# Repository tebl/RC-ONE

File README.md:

# KIM-1 Replica Computer
Along the years I've built quite a few computers, some bought as kits from various vendors and some I've even designed myself based on designs described in good old books or other technical resources - above all, there's always been one I really wanted above all of them: the KIM-1! 

Originally created by MOS in order to show off their new 6502-processor, it was a success that tapped into a market they probably never knew themselves was growing into a force to be reckoned with - the homecomputing market! Later bought up by little-known typewriter-manufacturer *Commodore*, the KIM-1 is an iconic piece of hardware and since I can't afford to buy one I'll build one instead.

The original unit cost 245$ assembled with everything you needed to get started, it had six segment displays for outputting information and a 24-key keypad onboard. CPU ran at an incredible 1 Mhz, it had a complete monitor in 2K of ROM, 1K of static RAM as well as an additional 128 bytes of RAM. You got 15 additional I/O lines to play with, all on a single PCB.

# RC-ONE
I however don't have that amount of money to play with, PCB prices skyrocket past 100x100 mm so I've separated functionality into separate boards so that each version would cost only around 5$ per piece instead. It means it's no longer a single board computer, but if it means more people can build it as a fun project then that's a plus in my book. The main setup does not include the additional 15 I/O lines due to space requirements, but you can add those back to the system by including the 65K Expansion (in addition to the backplane module) if you want to. If you just want to play around with the system and try your hand at machine language coding, you can get started with the CPU board, UI board and a keypad module.

As a classic microcomputer, I've gone ahead and created the obligatory memory map for your perusal - the highlights are shown below, but you'll find the complete set of information in the documentation section ([ODS](https://github.com/tebl/RC-ONE/raw/master/documentation/memory_map.ods)- or [PDF](https://github.com/tebl/RC-ONE/raw/master/documentation/memory_map.pdf)-format). Some of the functions have been shifted physically, but in the end the system should be functionally identical to an original system and able to run code without requireing changes.

The system is highly expandable, with the [65K Expansion board](https://github.com/tebl/RC-ONE/tree/master/RC1%2065K%20Expansion) in place you'll get better utilization of the components already on the CPU board as well as the ability to add additional modules to the system with an additional backplane also in place. See *System modules* below for a list of modules required for a complete system, optional modules available as well as modules for other systems that are compatible with the RC-ONE computer.

A lot of the work I've done couldn't have been completed without the work previously done by Ruud Baltissen, you can compare the schematics he did for the original KIM-1 computer and his more modern recreation of it by studying his [Build your own KIM-1](http://www.baltissen.org/newhtm/buildkim.htm) page.

## Project status
The RC-ONE computer is operational, it can be used to enter and run code via the keypad and can output to the displays as expected and for many this will be all that's needed to have fun with it as a replica of the KIM-1. Some sections are still being worked on, mainly those that deal with the TTY mode and tape functionality - see [TODO](https://github.com/tebl/RC-ONE/blob/master/TODO.md) for an overview of things I'd like to see done sometime in the future!

## System modules
As mentioned earlier there are a few different modules available for the system, some will be required to make the system function and others is considered optional and can be added if you want that extra piece of 70s-technology to play around with. There may be additional modules in the project files, but the ones I've added here are the ones that can be considered ready. As modules are being worked on over time, I've also added an order link to the modules so that you can get the last version I know worked. For more information about the specific module, including schematic and a list of parts you'd need to build it - click the name of the module!

Note that due to the similarities with the [RC6502  Apple 1 Replica](https://github.com/tebl/RC6502-Apple-1-Replica), quite a few of the modules developed for that system will also work with the RC-ONE - the ones I've tested and use with the system have also been linked below.

| Module    | RC-ONE | RC-ONE 65K | Order |
| --------- | ------ | ---------- | ----- |
| [RC-ONE CPU](https://github.com/tebl/RC-ONE/tree/master/RC1%20CPU) | required | required | [PCBWay](https://www.pcbway.com/project/shareproject/RC_ONE_KIM_1_Replica__CPU_module_.html) |
| [RC-ONE User Interface](https://github.com/tebl/RC-ONE/tree/master/RC1%20UI) | required | required | [PCBWay](https://www.pcbway.com/project/shareproject/RC_ONE_KIM_1_Replica__UI_revision_C_.html) |
| [RC-ONE Keypad SX](https://github.com/tebl/RC-ONE/tree/master/RC1%20Keypad) | required * | required * | [PCBWay](https://www.pcbway.com/project/shareproject/RC_ONE_Keypad_SX.html?inviteid=88707) |
| [RC-ONE Keypad MX](https://github.com/tebl/RC-ONE/tree/master/RC1%20Keypad%20MX) | required * | required * | [PCBWay](https://www.pcbway.com/project/shareproject/RC_ONE_Keypad_MX.html) |
| [RC-ONE 65K Expansion](https://github.com/tebl/RC-ONE/tree/master/RC1%2065K%20Expansion) |  | required | [PCBWay](https://www.pcbway.com/project/shareproject/RC_ONE_65K_Expansion.html) |
| [RC-ONE 8K ExRAM](https://github.com/tebl/RC-ONE/tree/master/RC1%208K%20ExRAM) |  | optional | |
| [RC6502 Backplane](https://github.com/tebl/RC6502-Apple-1-Replica/tree/master/RC6502%20Backplane)  |  | required | [PCBWay](https://www.pcbway.com/project/shareproject/RC6502_Apple_1_Replica__Backplane_module_revision_A_.html?inviteid=88707) |
| [RC6502 Prototyping module](https://github.com/tebl/RC6502-Apple-1-Replica/tree/master/RC6502%20Prototyping) |  | optional | [PCBWay](https://www.pcbway.com/project/shareproject/RC6502_Apple_1_Replica__Module_prototyping_board_.html?inviteid=88707) |
| [6502 Project Platform](https://github.com/tebl/RC-Project-Board) | optional | optional | [PCBWay](https://www.pcbway.com/project/shareproject/6502_Project_Platform__RC6502__RC_ONE__RC6802_.html?inviteid=88707) |
| [6502 Games Board](https://github.com/tebl/RC-Project-Board/tree/master/projects/GB-001%20Game%20Board) | | optional** | [PCBWay](https://www.pcbway.com/project/shareproject/6502_Games_Board.html)
| [6502 Games Platform](https://github.com/tebl/RC-Project-Board/tree/master/platforms/PP%206502%20Game%20Board) | | optional** | [PCBWay](https://www.pcbway.com/project/shareproject/6502_Games_Platform.html)

*) Only one Keypad module is required, the MX version is a lot more comfortable to use though it comes at an increased cost.
**) You need [6502 Games Platform](https://github.com/tebl/RC-Project-Board/tree/master/platforms/PP%206502%20Game%20Board) and 6502 Game Board to build the 6502 Games hardware, originally created by Rodnay Zaks in his book [6502 Games](https://archive.org/details/6502GamesRodnayZaks/mode/2up). To use them with the RC-ONE you also require the [65K Expansion](https://github.com/tebl/RC-ONE/tree/master/RC1%2065K%20Expansion) installed.

If you would like to have a copy of one or more modules (usually 5$ per module), consider using the order links listed above - that way you also support the development of these boards while doing so. Alternatively, you can also zip up the contents of the export directory for each module and give that to your favourite PCB fabrication plant (I use [PCBWay](https://www.pcbway.com/setinvite.aspx?inviteid=88707) instead. Note that since I'm always tinkering with things, this repository may contain changes that I've not yet tested!

## Tell me more!
You'll find a lot of additional technical information belonging to each of the various modules by clicking on them from the table in the previous section, but those are mainly for reference when using or building them. For that reason I've also taken the time to write a somewhat acceptable attempt at a [manual](https://github.com/tebl/RC-ONE/blob/master/Manual.md), it should be able to get you started at both understanding not only how to use the computer, but also give you a more concise idea about what a KIM-1 computer (or replica) actually is.

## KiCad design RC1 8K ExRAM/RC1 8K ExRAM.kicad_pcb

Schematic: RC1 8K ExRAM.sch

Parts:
A1: Arduino_Nano_v3.x; Arduino_Nano
C1, C2, C3, C4, C5, C6, C7, C8: 100nF; C_Disc_D4.7mm_W2.5mm_P5.00mm
D1: BUSY; LED_D5.0mm
D2: DATA; LED_D5.0mm
D3: CLK; LED_D5.0mm
D4: 1n914; D_DO-35_SOD27_P7.62mm_Horizontal
J1: Expansion; Pin_Header_Angled_1x39_Pitch2.54mm
J2: ADDRESS; Pin_Header_Straight_2x09_Pitch2.54mm
JP1: USB_PWR; Pin_Header_Straight_1x02_Pitch2.54mm
JP2: ReadOnly; Pin_Header_Straight_1x03_Pitch2.54mm
R1, R2, R3: 220; R_Axial_DIN0207_L6.3mm_D2.5mm_P10.16mm_Horizontal
R4, R5, R6, R7: 10k; R_Axial_DIN0207_L6.3mm_D2.5mm_P10.16mm_Horizontal
U1: 74LS138; DIP-16_W7.62mm_Socket
U2: 74LS00; DIP-14_W7.62mm_Socket
U3, U4: 74HC595; DIP-16_W7.62mm_Socket
U5: HM62256BLP-7; DIP-28_W15.24mm_Socket
U6, U7: 74LS244; DIP-20_W7.62mm_Socket
U8: 74LS245; DIP-20_W7.62mm_Socket

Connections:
/8K1: J2.1, U1.14 (O1)
/8K2: J2.3, U1.13 (O2)
/8K3: J2.5, U1.12 (O3)
/8K4: J2.7, U1.11 (O4)
/8K5: J2.9, U1.10 (O5)
/8K6: J2.11, U1.9 (O6)
/8K7: J2.13, U1.7 (O7)
/A0: J1.16 (A0), U6.2 (I0a)
/A1: J1.15 (A1), U6.4 (I1a)
/A2: J1.14 (A2), U6.6 (I2a)
/A3: J1.13 (A3), U6.8 (I3a)
/A4: J1.12 (A4), U6.11 (I0b)
/A5: J1.11 (A5), U6.13 (I1b)
/A6: J1.10 (A6), U6.15 (I2b)
/A7: J1.9 (A7), U6.17 (I3b)
/A8: J1.8 (A8), U7.2 (I0a)
/A9: J1.7 (A9), U7.4 (I1a)
/A10: J1.6 (A10), U7.6 (I2a)
/A11: J1.5 (A11), U7.8 (I3a)
/A12: J1.4 (A12), U7.11 (I0b)
/A13: J1.3 (A13), U1.1 (A0)
/A14: J1.2 (A14), U1.2 (A1)
/A15: J1.1 (A15), U1.3 (A2)
/D0: J1.27 (D0), U8.18 (B0)
/D1: J1.28 (D1), U8.17 (B1)
/D2: J1.29 (D2), U8.16 (B2)
/D3: J1.30 (D3), U8.15 (B3)
/D4: J1.31 (D4), U8.14 (B4)
/D5: J1.32 (D5), U8.13 (B5)
/D6: J1.33 (D6), U8.12 (B6)
/D7: J1.34 (D7), U8.11 (B7)
/EX_A0: U3.15 (QA), U5.10, U6.18 (O0a)
/EX_A1: U3.1 (QB), U5.9, U6.16 (O1a)
/EX_A2: U3.2 (QC), U5.8, U6.14 (O2a)
/EX_A3: U3.3 (QD), U5.7, U6.12 (O3a)
/EX_A4: U3.4 (QE), U5.6, U6.9 (O0b)
/EX_A5: U3.5 (QF), U5.5, U6.7 (O1b)
/EX_A6: U3.6 (QG), U5.4, U6.5 (O2b)
/EX_A7: U3.7 (QH), U5.3, U6.3 (O3b)
/EX_A8: U4.15 (QA), U5.25, U7.18 (O0a)
/EX_A9: U4.1 (QB), U5.24, U7.16 (O1a)
/EX_A10: U4.2 (QC), U5.21, U7.14 (O2a)
/EX_A11: U4.3 (QD), U5.23, U7.12 (O3a)
/EX_A12: U4.4 (QE), U5.2, U7.9 (O0b)
/EX_A13: A1.19, R6.1, U5.26
/EX_A14: A1.20, R5.1, U5.1
/EX_D0: A1.9, U5.11, U8.2 (A0)
/EX_D1: A1.10, U5.12, U8.3 (A1)
/EX_D2: A1.11, U5.13, U8.4 (A2)
/EX_D3: A1.12, U5.15, U8.5 (A3)
/EX_D4: A1.13, U5.16, U8.6 (A4)
/EX_D5: A1.14, U5.17, U8.7 (A5)
/EX_D6: A1.15, U5.18, U8.8 (A6)
/EX_D7: A1.16, U5.19, U8.9 (A7)
/EX_R/~W: A1.21, JP2.2, R7.1, U5.27
/EX_~CS: A1.24, U5.20, U7.3 (O3b); also elsewhere on the board
/PHI2: J1.19 (PHI2), U1.6 (E3)
/R/~W: J1.24 (RW), U7.13 (I1b), U8.1 (A->B)
/RESET: A1.22, J1.20 (RESET)
BUSY: R1.2, U2.6
CONTROL: A1.8, R4.1, U2.4, U2.5, U2.9, U3.13 (G), U4.13 (G)
K0_EXT: J1.36 (RX), J2.15
K7_EXT: J1.37 (NMI), J2.17
unnamed: A1.27, D4.1, JP1.1
unnamed: D1.2, R1.1
unnamed: D2.2, R2.1
unnamed: D3.2, R3.1
unnamed: J2.2, J2.4, J2.6, J2.8, J2.10, J2.12, J2.14, J2.16, J2.18, U2.1, U2.2
unnamed: JP2.1, U7.5 (O2b)
unnamed: JP2.3, U7.7 (O1b)
unnamed: U2.3, U2.10
unnamed: U3.9 (~QH), U4.14 (SER)
SHIFT_CLK: A1.6, R3.2, U3.11 (SRCLK), U4.11 (SRCLK)
SHIFT_DATA: A1.5, R2.2, U3.14 (SER)
SHIFT_LATCH: A1.7, U3.12 (RCLK), U4.12 (RCLK)
VMEM: C5.1, R7.2, U5.28; also elsewhere on the board
~RC1_CS: U2.8, U6.1 (OEa), U6.19 (OEb), U7.1 (OEa), U7.17 (I3b), U7.19 (OEb), U8.19 (CE)

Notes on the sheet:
RC-ONE 8K ExRAM
$E000
$2000
$4000
$6000
$8000
$A000
$C000
RAM SELECT
ROM SELECT
HI allows 6502 access to RAM
RC-ONE is accessing data from memory.
Based on an idea for an EEPROM programmer by Ben Eater, this adapts the idea to loading data into static RAM via an Arduino Nano. The Nano can block the 6502 from accessing the memory while data is being loaded, ReadOnly jumper can be used to keep 6502 from being able to change the data.
ExRAM is controlling memory

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
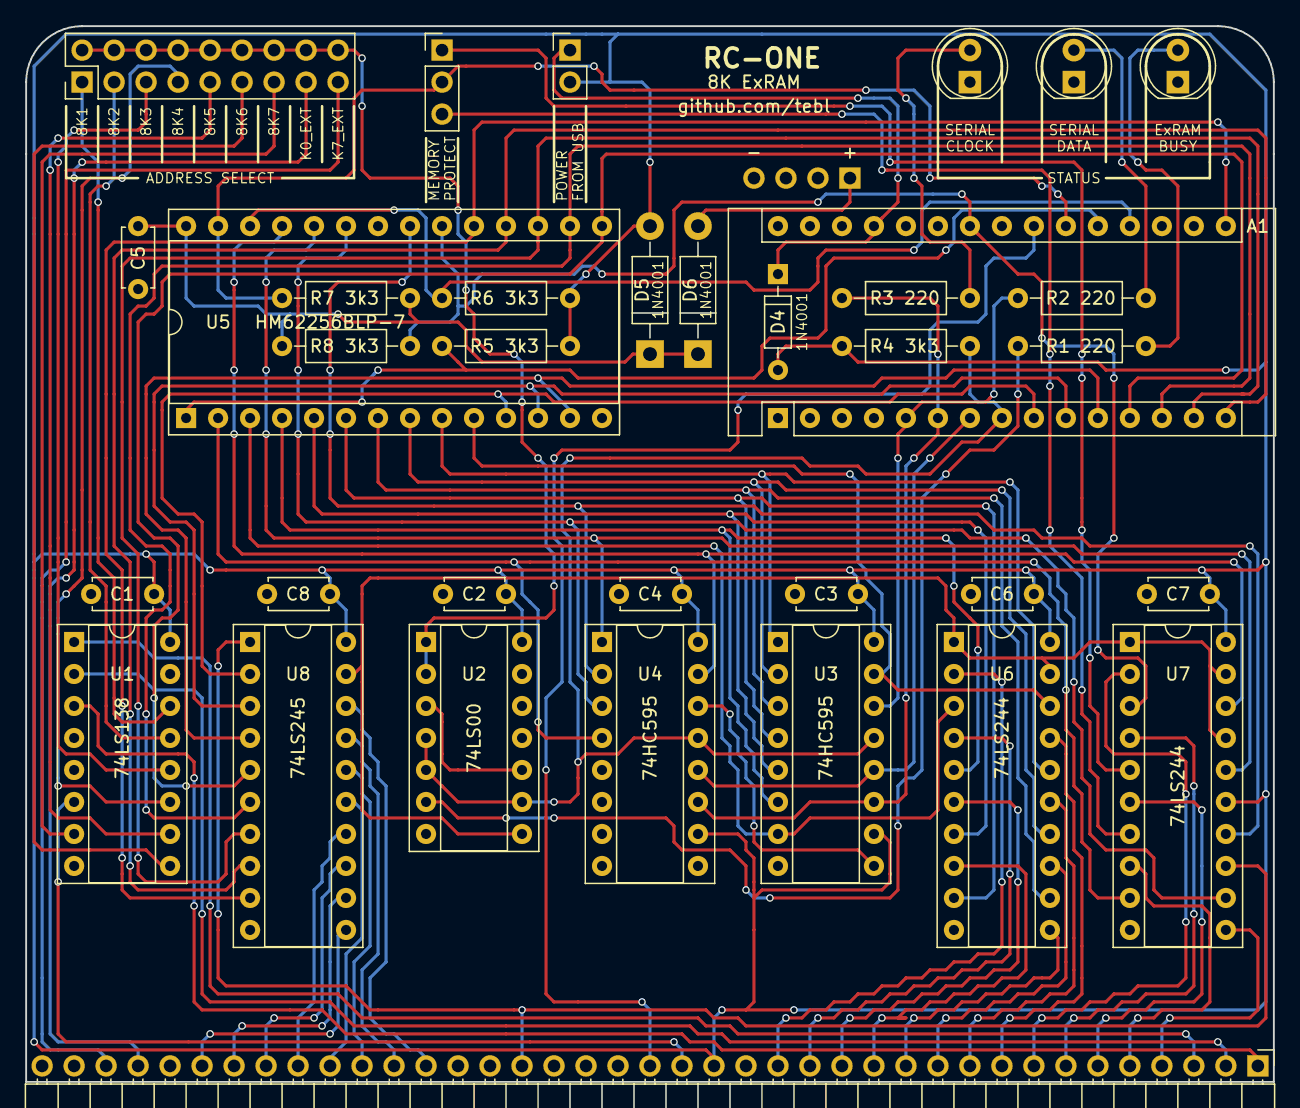
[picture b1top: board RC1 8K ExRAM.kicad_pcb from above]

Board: 2 copper layers, 99.1 x 83.8 mm, 36 parts (1 on the bottom side), 80 nets.

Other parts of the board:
D5, D6: 1N4001; D_DO-41_SOD81_P10.16mm_Horizontal
J3: BATTERY; Pin_Header_Angled_1x04_Pitch2.54mm
R8: 3k3; R_Axial_DIN0207_L6.3mm_D2.5mm_P10.16mm_Horizontal

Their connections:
/BATTERY: D6.2, J3.1
/EX_~CS: R8.1; also elsewhere on the board
VMEM: D5.1, D6.1, R8.2; also elsewhere on the board

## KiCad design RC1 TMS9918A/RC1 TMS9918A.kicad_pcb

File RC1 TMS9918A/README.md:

# RC-ONE TMS9918A

**This design is untested!**

Display card based on the TMS9918A chip created by Texas Instruments.

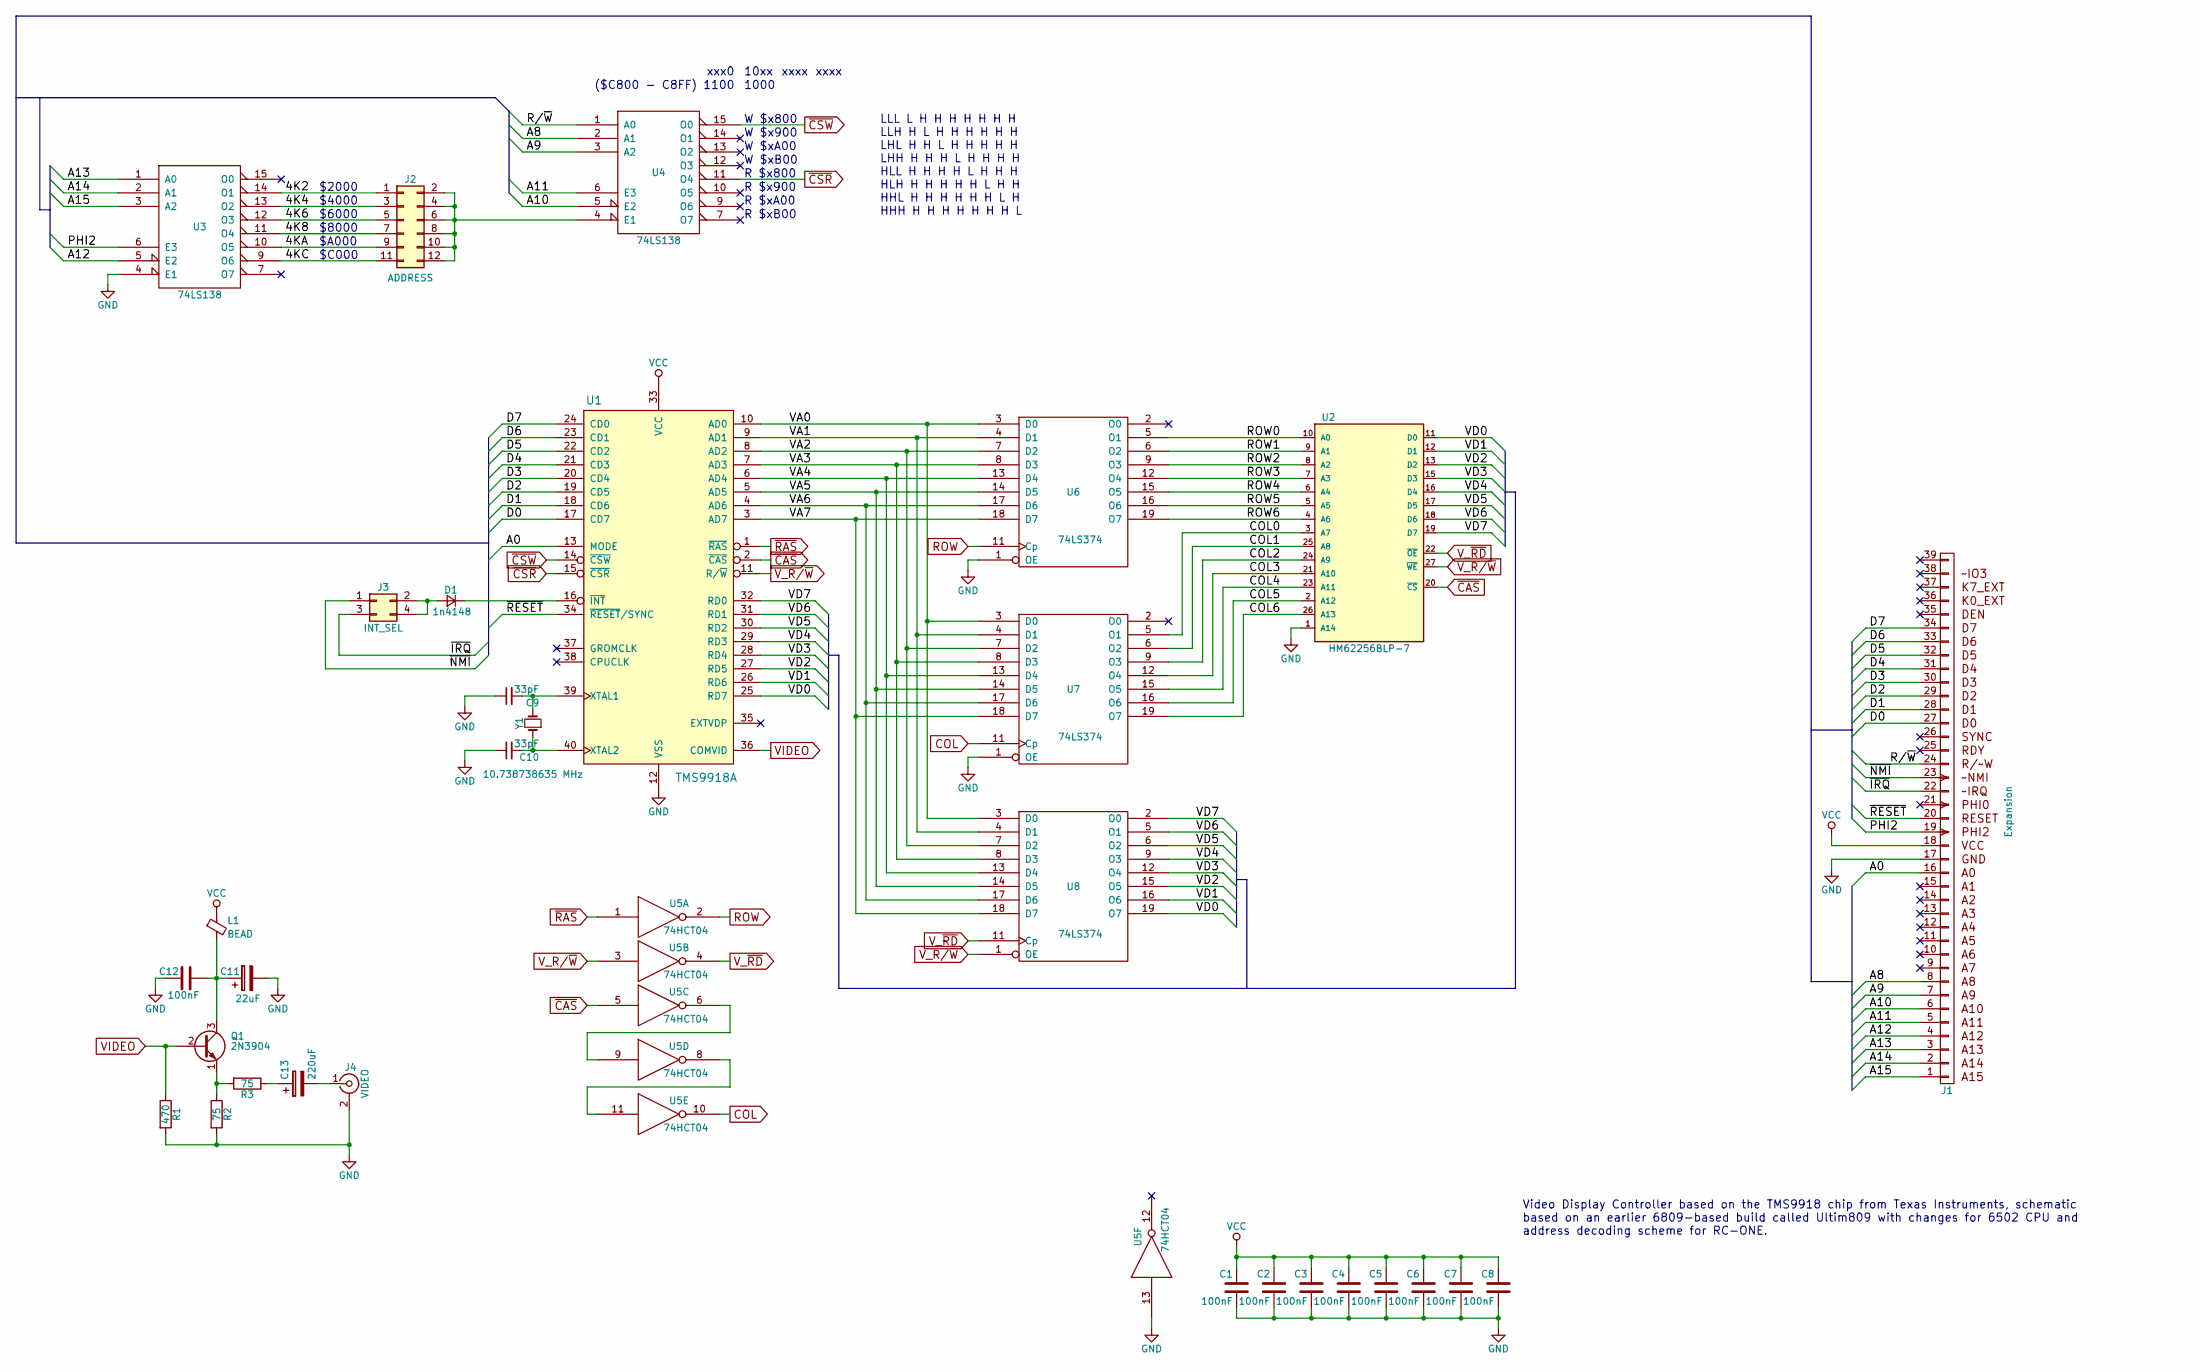
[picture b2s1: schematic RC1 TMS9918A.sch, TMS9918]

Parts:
C1, C2, C3, C4, C5, C6, C7, C8, C12: 100nF; C_Disc_D4.7mm_W2.5mm_P5.00mm
C9, C10: 33pF; C_Disc_D4.7mm_W2.5mm_P5.00mm
C11: 22uF; CP_Radial_D5.0mm_P2.50mm
C13: 220uF; CP_Radial_D5.0mm_P2.50mm
D1: 1n4148; D_DO-35_SOD27_P7.62mm_Horizontal
J1: Expansion; Pin_Header_Angled_1x39_Pitch2.54mm
J2: ADDRESS; Pin_Header_Straight_2x06_Pitch2.54mm
J3: INT_SEL; Pin_Header_Straight_2x02_Pitch2.54mm
J4: VIDEO; CUI_RCJ-013
L1: BEAD; L_Axial_L7.0mm_D3.3mm_P10.16mm_Horizontal_Fastron_MICC
Q1: 2N3904; TO-92_Molded_Narrow
R1: 470; R_Axial_DIN0207_L6.3mm_D2.5mm_P10.16mm_Horizontal
R2, R3: 75; R_Axial_DIN0207_L6.3mm_D2.5mm_P10.16mm_Horizontal
U1: TMS9918A; DIP-40_W15.24mm_Socket_LongPads
U2: HM62256BLP-7; DIP-28_W15.24mm_Socket_LongPads
U3, U4: 74LS138; DIP-16_W7.62mm_Socket
U5: 74HCT04; DIP-14_W7.62mm_Socket
U6, U7, U8: 74LS374; DIP-20_W7.62mm_Socket
Y1: 10.738738635 MHz; Crystal_HC49-4H_Vertical

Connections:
/4K2: J2.1, U3.14 (O1)
/4K4: J2.3, U3.13 (O2)
/4K6: J2.5, U3.12 (O3)
/4K8: J2.7, U3.11 (O4)
/4KA: J2.9, U3.10 (O5)
/4KC: J2.11, U3.9 (O6)
/A0: J1.16 (A0), U1.13 (MODE)
/A8: J1.8 (A8), U4.2 (A1)
/A9: J1.7 (A9), U4.3 (A2)
/A10: J1.6 (A10), U4.5 (E2)
/A11: J1.5 (A11), U4.6 (E3)
/A12: J1.4 (A12), U3.5 (E2)
/A13: J1.3 (A13), U3.1 (A0)
/A14: J1.2 (A14), U3.2 (A1)
/A15: J1.1 (A15), U3.3 (A2)
/COL0: U2.3 (A7), U7.5 (O1)
/COL1: U2.25 (A8), U7.6 (O2)
/COL2: U2.24 (A9), U7.9 (O3)
/COL3: U2.21 (A10), U7.12 (O4)
/COL4: U2.23 (A11), U7.15 (O5)
/COL5: U2.2 (A12), U7.16 (O6)
/COL6: U2.26 (A13), U7.19 (O7)
/D0: J1.27 (D0), U1.17 (CD7)
/D1: J1.28 (D1), U1.18 (CD6)
/D2: J1.29 (D2), U1.19 (CD5)
/D3: J1.30 (D3), U1.20 (CD4)
/D4: J1.31 (D4), U1.21 (CD3)
/D5: J1.32 (D5), U1.22 (CD2)
/D6: J1.33 (D6), U1.23 (CD1)
/D7: J1.34 (D7), U1.24 (CD0)
/PHI2: J1.19 (PHI2), U3.6 (E3)
/R/~W: J1.24 (RW), U4.1 (A0)
/ROW0: U2.10 (A0), U6.5 (O1)
/ROW1: U2.9 (A1), U6.6 (O2)
/ROW2: U2.8 (A2), U6.9 (O3)
/ROW3: U2.7 (A3), U6.12 (O4)
/ROW4: U2.6 (A4), U6.15 (O5)
/ROW5: U2.5 (A5), U6.16 (O6)
/ROW6: U2.4 (A6), U6.19 (O7)
/VA0: U1.10 (AD0), U6.3 (D0), U7.3 (D0), U8.3 (D0)
/VA1: U1.9 (AD1), U6.4 (D1), U7.4 (D1), U8.4 (D1)
/VA2: U1.8 (AD2), U6.7 (D2), U7.7 (D2), U8.7 (D2)
/VA3: U1.7 (AD3), U6.8 (D3), U7.8 (D3), U8.8 (D3)
/VA4: U1.6 (AD4), U6.13 (D4), U7.13 (D4), U8.13 (D4)
/VA5: U1.5 (AD5), U6.14 (D5), U7.14 (D5), U8.14 (D5)
/VA6: U1.4 (AD6), U6.17 (D6), U7.17 (D6), U8.17 (D6)
/VA7: U1.3 (AD7), U6.18 (D7), U7.18 (D7), U8.18 (D7)
/VD0: U1.25 (RD7), U2.11 (D0), U8.19 (O7)
/VD1: U1.26 (RD6), U2.12 (D1), U8.16 (O6)
/VD2: U1.27 (RD5), U2.13 (D2), U8.15 (O5)
/VD3: U1.28 (RD4), U2.15 (D3), U8.12 (O4)
/VD4: U1.29 (RD3), U2.16 (D4), U8.9 (O3)
/VD5: U1.30 (RD2), U2.17 (D5), U8.6 (O2)
/VD6: U1.31 (RD1), U2.18 (D6), U8.5 (O1)
/VD7: U1.32 (RD0), U2.19 (D7), U8.2 (O0)
/~IRQ: J1.22 (IRQ), J3.3
/~NMI: J1.23 (PHI1), J3.1
/~RESET: J1.20 (RESET), U1.34 (~RESET~/SYNC)
COL: U5.10, U7.11 (Cp)
GND: C1.2, C2.2, C3.2, C4.2, C5.2, C6.2, C7.2, C8.2, C9.1, C10.1, C11.2, C12.1, J1.17, J4.2 (Ext), R1.2, R2.2, U1.12 (VSS), U2.1 (A14), U2.14 (GND), U3.4 (E1), U3.8 (GND), U4.8 (GND), U5.7 (GND), U5.13, U6.1 (OE), U6.10 (GND), U7.1 (OE), U7.10 (GND), U8.10 (GND)
unnamed: C9.2, U1.39 (XTAL1), Y1.2
unnamed: C10.2, U1.40 (XTAL2), Y1.1
unnamed: C11.1, C12.2, L1.2, Q1.3 (C)
unnamed: C13.1, R3.1
unnamed: C13.2, J4.1 (In)
unnamed: D1.1 (K), U1.16 (~INT~)
unnamed: D1.2 (A), J3.2, J3.4
unnamed: J2.2, J2.4, J2.6, J2.8, J2.10, J2.12, U4.4 (E1)
unnamed: Q1.1 (E), R2.1, R3.2
unnamed: U5.6, U5.9
unnamed: U5.8, U5.11
ROW: U5.2, U6.11 (Cp)
VCC: C1.1, C2.1, C3.1, C4.1, C5.1, C6.1, C7.1, C8.1, J1.18, L1.1, U1.33 (VCC), U2.28 (VCC), U3.16 (VCC), U4.16 (VCC), U5.14 (VCC), U6.20 (VCC), U7.20 (VCC), U8.20 (VCC)
VIDEO: Q1.2 (B), R1.1, U1.36 (COMVID)
V_R/~W: U1.11 (R/~W~), U2.27 (~WE), U5.3, U8.1 (OE)
V_~RD: U2.22 (~OE), U5.4, U8.11 (Cp)
~CAS: U1.2 (~CAS~), U2.20 (~CS), U5.5
~CSR: U1.15 (~CSR~), U4.11 (O4)
~CSW: U1.14 (~CSW~), U4.15 (O0)
~RAS: U1.1 (~RAS~), U5.1

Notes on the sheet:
$2000
$4000
$6000
$8000
$A000
$C000
W $x800
LLL L H H H H H H H LLH H L H H H H H H LHL H H L H H H H H LHH H H H L H H H H HLL H H H H L H H H HLH H H H H H L H H HHL H H H H H H L H HHH H H H H H H H L
xxx0
10xx
xxxx
W $x900
W $xA00
W $xB00
R $x800
R $x900
R $xA00
R $xB00
1100
1000
($C800 - C8FF)
Video Display Controller based on the TMS9918 chip from Texas Instruments, schematic based on an earlier 6809-based build called Ultim809 with changes for 6502 CPU and address decoding scheme for RC-ONE.

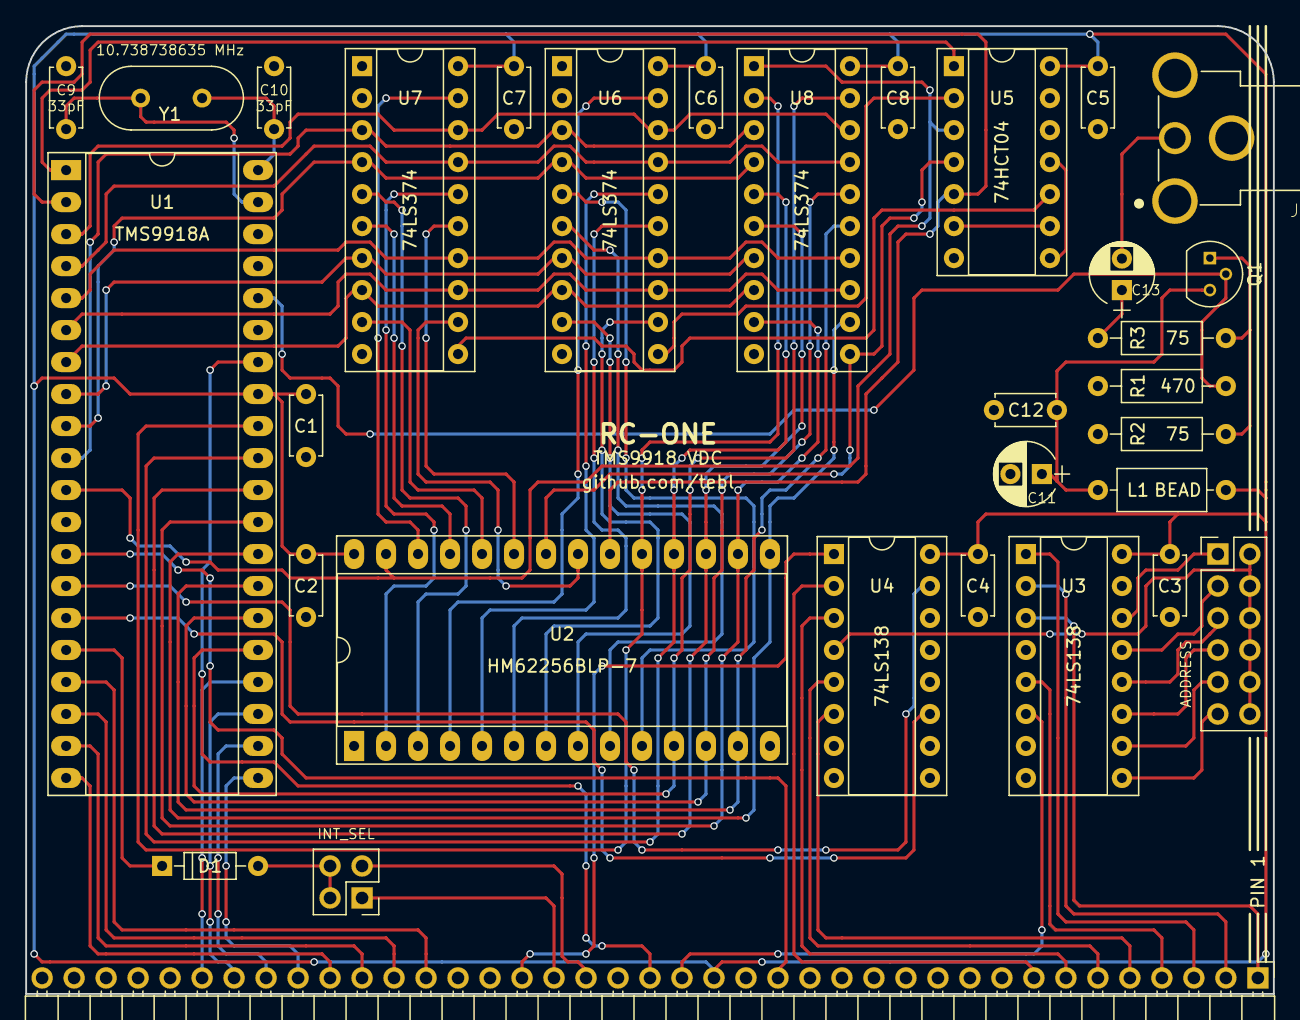
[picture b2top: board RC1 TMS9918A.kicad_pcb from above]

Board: 2 copper layers, 99.1 x 76.8 mm, 32 parts (0 on the bottom side), 80 nets.

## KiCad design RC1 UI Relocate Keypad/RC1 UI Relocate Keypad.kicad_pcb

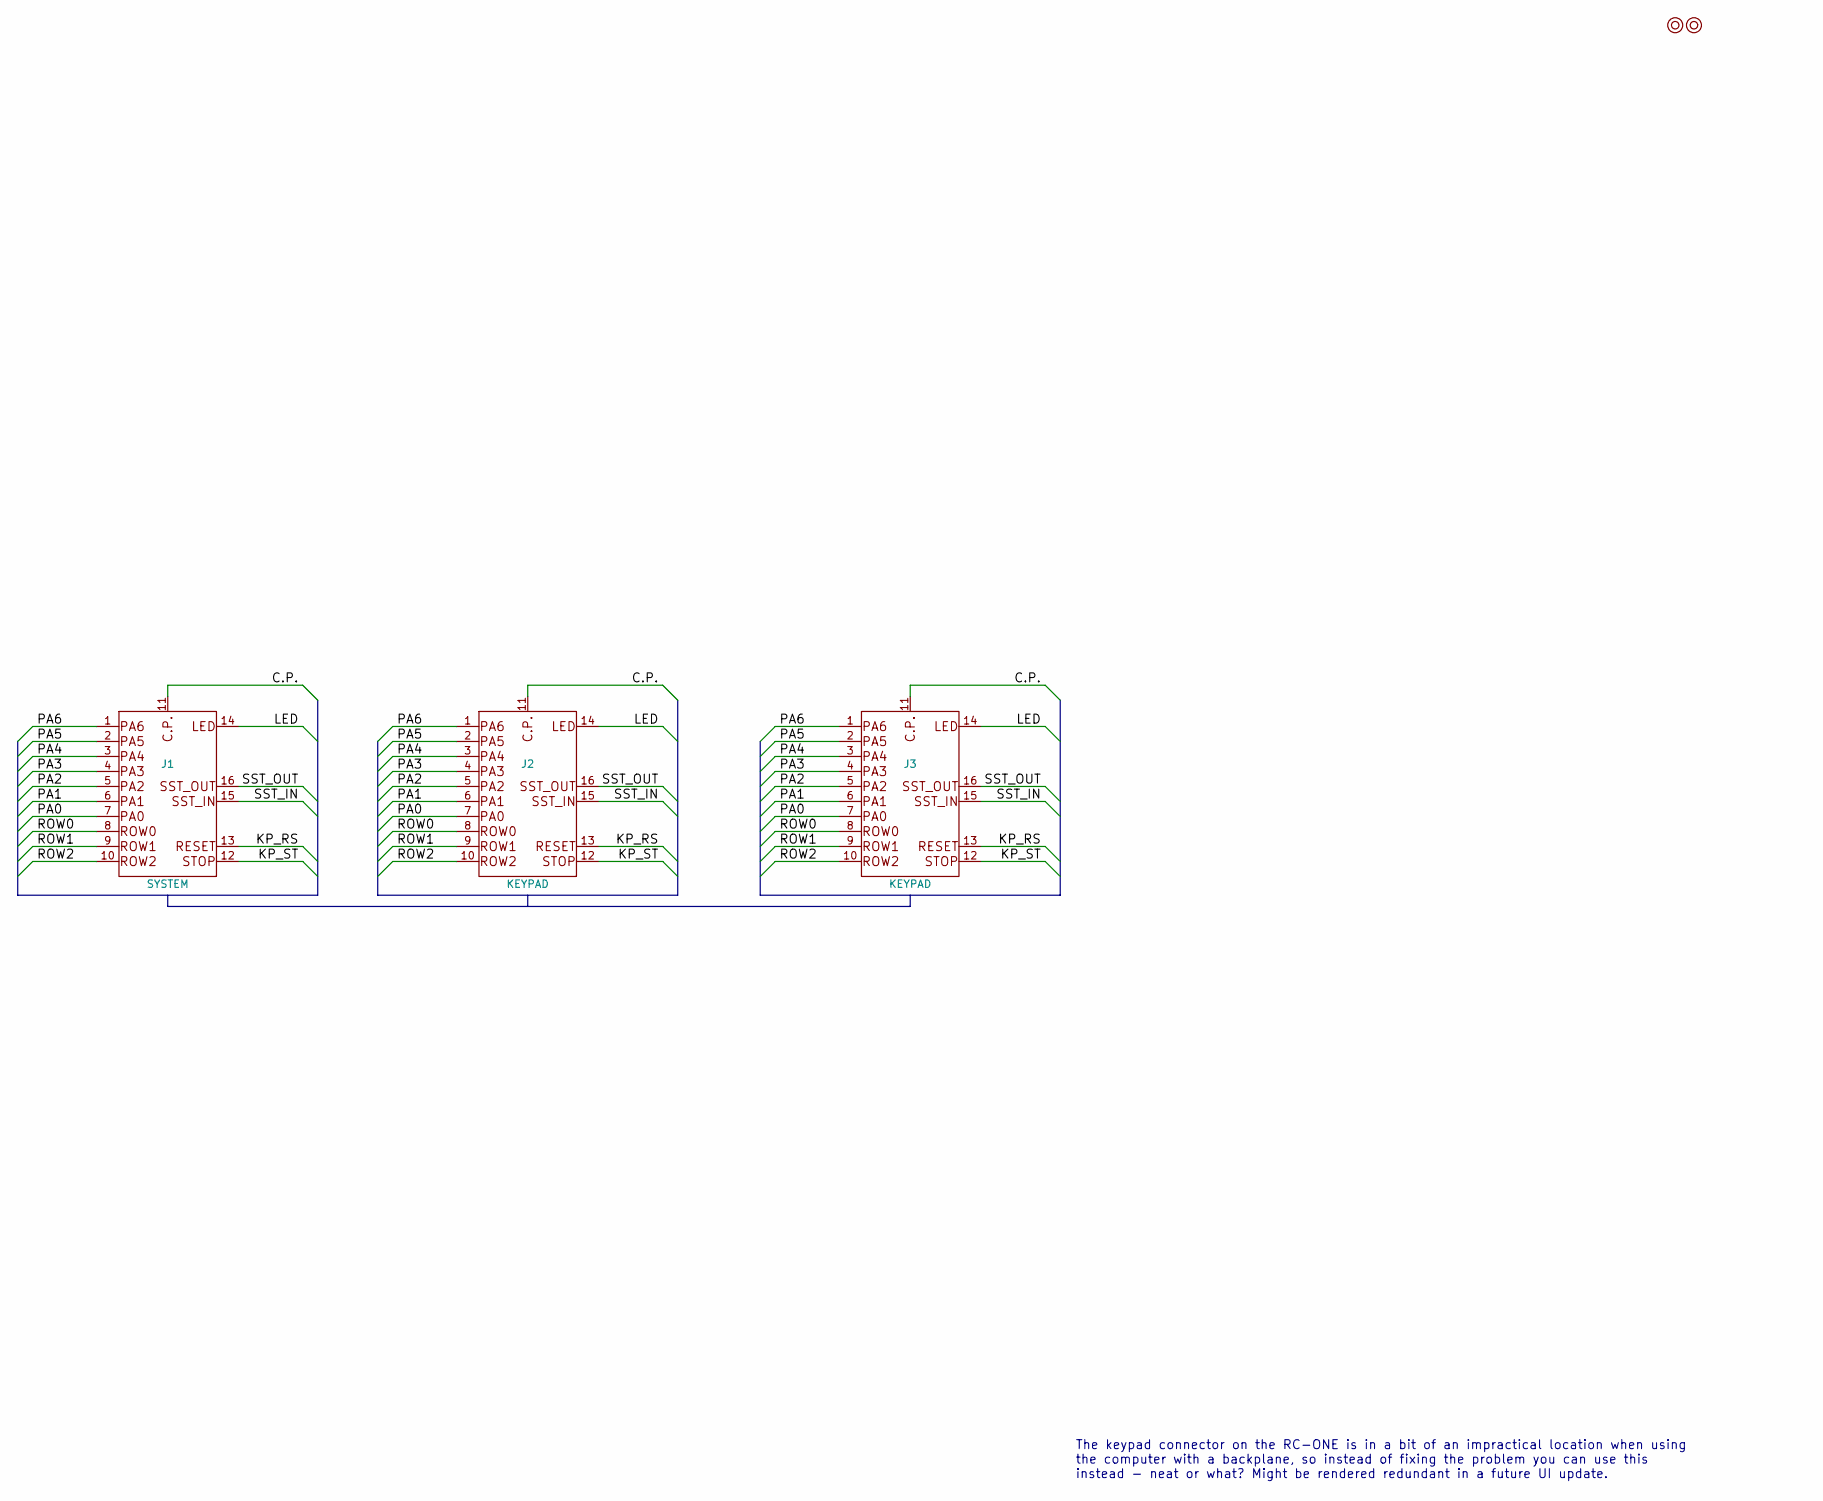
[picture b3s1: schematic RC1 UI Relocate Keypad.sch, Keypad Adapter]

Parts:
J1: SYSTEM; Pin_Header_Straight_2x08_Pitch2.54mm
J2, J3: KEYPAD; Pin_Header_Straight_2x08_Pitch2.54mm
M1, M4: Mounting; 1pin

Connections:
/C.P.: J1.11, J2.11, J3.11
/KP_RS: J1.13, J2.13, J3.13
/KP_ST: J1.12, J2.12, J3.12
/LED: J1.14, J2.14, J3.14
/PA0: J1.7, J2.7, J3.7
/PA1: J1.6, J2.6, J3.6
/PA2: J1.5, J2.5, J3.5
/PA3: J1.4, J2.4, J3.4
/PA4: J1.3, J2.3, J3.3
/PA5: J1.2, J2.2, J3.2
/PA6: J1.1, J2.1, J3.1
/ROW0: J1.8, J2.8, J3.8
/ROW1: J1.9, J2.9, J3.9
/ROW2: J1.10, J2.10, J3.10
/SST_IN: J1.15, J2.15, J3.15
/SST_OUT: J1.16, J2.16, J3.16

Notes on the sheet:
The keypad connector on the RC-ONE is in a bit of an impractical location when using the computer with a backplane, so instead of fixing the problem you can use this instead - neat or what? Might be rendered redundant in a future UI update.

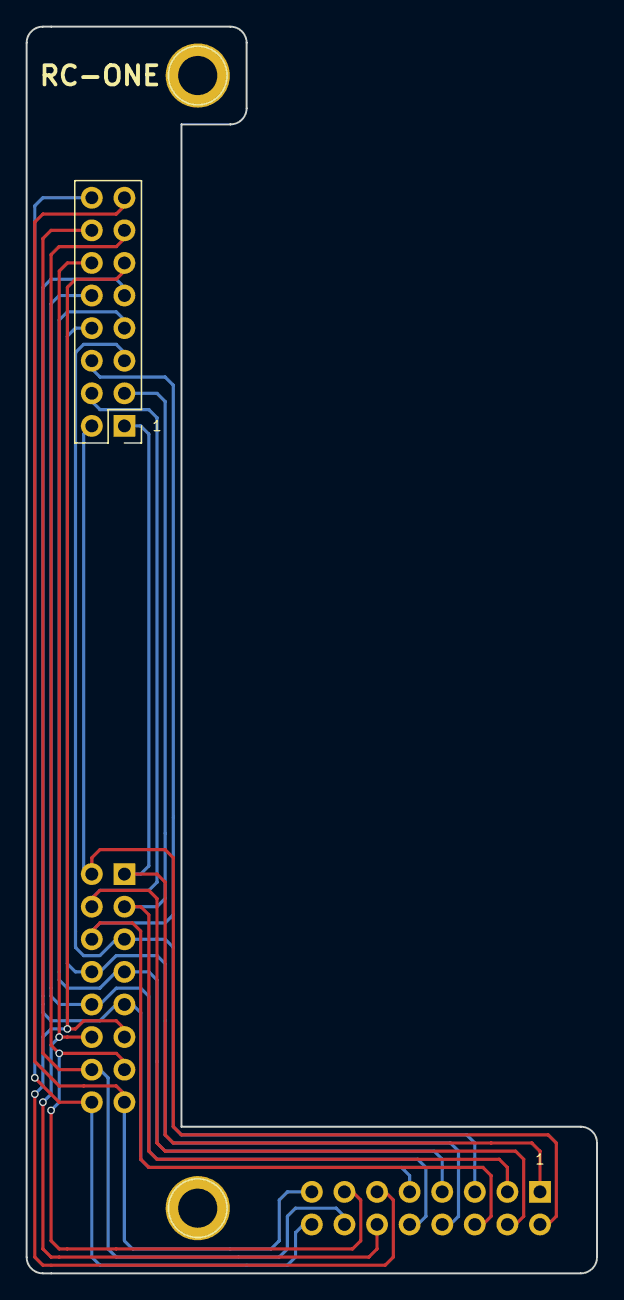
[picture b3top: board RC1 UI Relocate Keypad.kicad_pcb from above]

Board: 2 copper layers, 44.5 x 97.2 mm, 5 parts (1 on the bottom side), 16 nets.

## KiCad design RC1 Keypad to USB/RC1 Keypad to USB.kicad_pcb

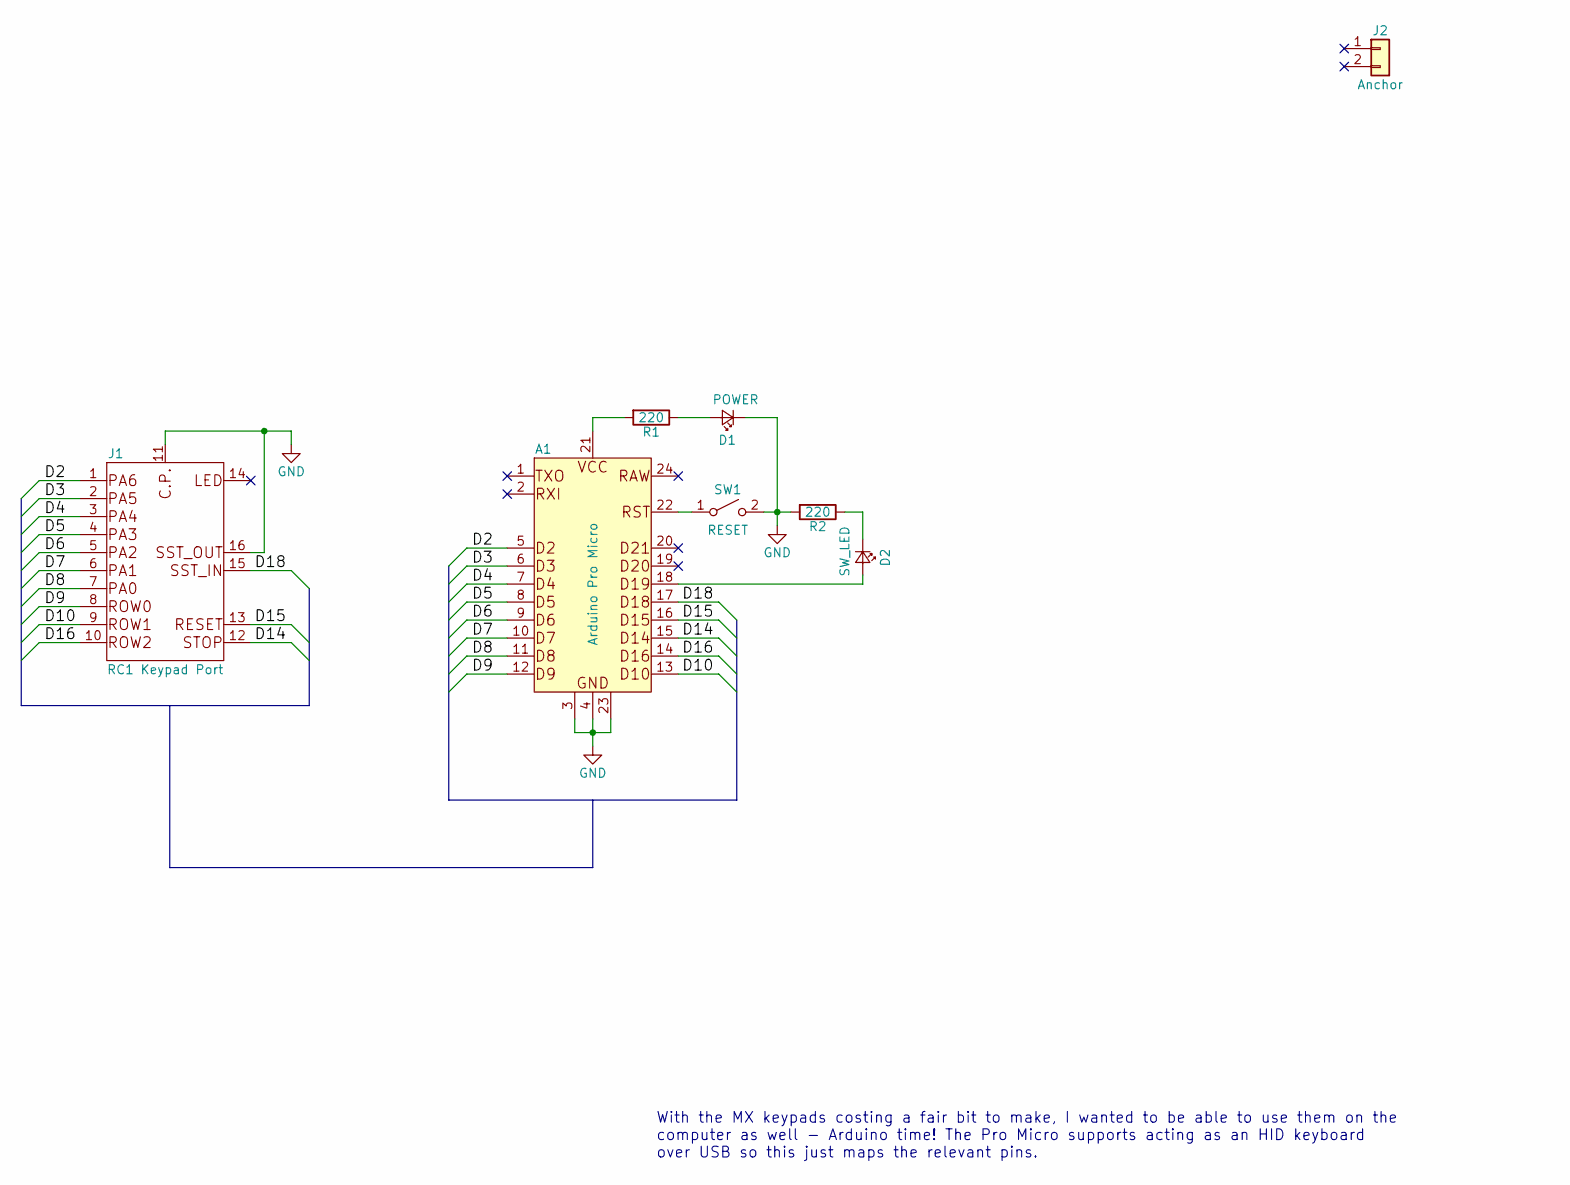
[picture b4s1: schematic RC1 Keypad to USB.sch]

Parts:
A1: Arduino Pro Micro; Arduino_Pro_Micro
D1: POWER; LED_D5.0mm
D2: SW_LED; LED_D5.0mm
J1: RC1 Keypad Port; Pin_Header_Straight_2x08_Pitch2.54mm
J2: Anchor; Pin_Header_Straight_1x02_Pitch2.54mm
R1, R2: 220; R_Axial_DIN0207_L6.3mm_D2.5mm_P10.16mm_Horizontal
SW1: RESET; SW_PUSH_6mm

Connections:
/D2: A1.5 (D2), J1.1
/D3: A1.6 (D3), J1.2
/D4: A1.7 (D4), J1.3
/D5: A1.8 (D5), J1.4
/D6: A1.9 (D6), J1.5
/D7: A1.10 (D7), J1.6
/D8: A1.11 (D8), J1.7
/D9: A1.12 (D9), J1.8
/D10: A1.13 (D10), J1.9
/D14: A1.15 (D14), J1.12
/D15: A1.16 (D15), J1.13
/D16: A1.14 (D16), J1.10
/D18: A1.17 (D18), J1.15
GND: A1.3 (GND), A1.4 (GND), A1.23 (GND), D1.1 (K), J1.11, J1.16, R2.2, SW1.2 (B)
unnamed: A1.18 (D19), D2.2 (A)
unnamed: A1.21 (VCC), R1.2
unnamed: A1.22 (RST), SW1.1 (A)
unnamed: D1.2 (A), R1.1
unnamed: D2.1 (K), R2.1

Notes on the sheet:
With the MX keypads costing a fair bit to make, I wanted to be able to use them on the computer as well - Arduino time! The Pro Micro supports acting as an HID keyboard over USB so this just maps the relevant pins.

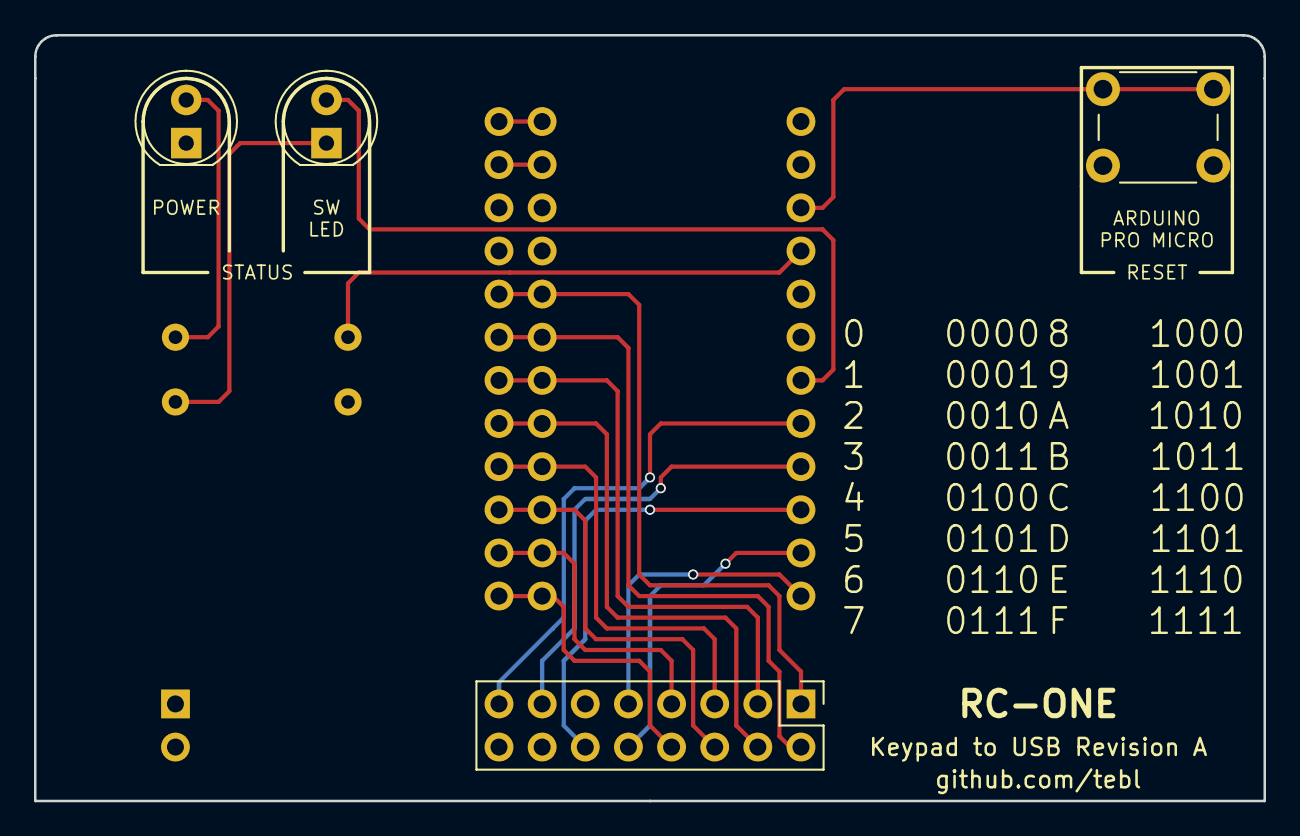
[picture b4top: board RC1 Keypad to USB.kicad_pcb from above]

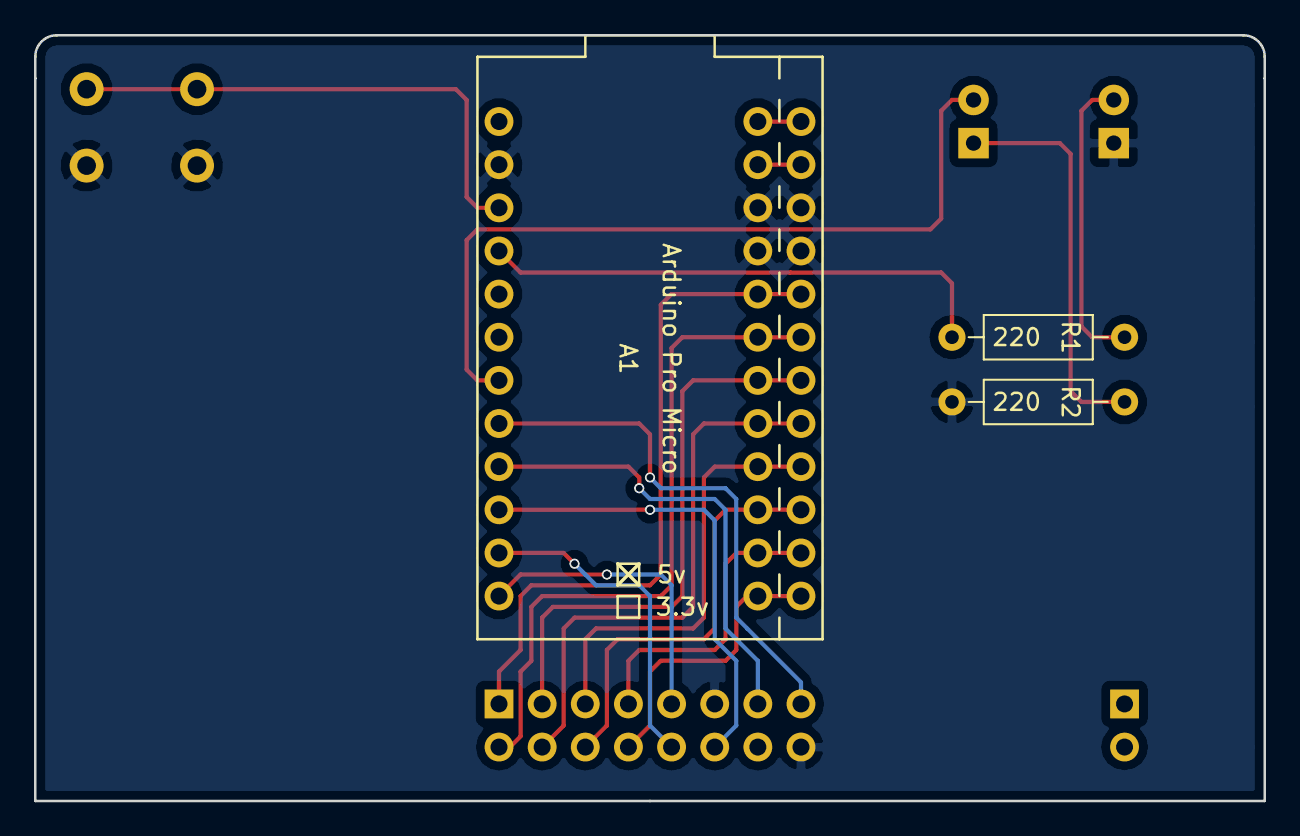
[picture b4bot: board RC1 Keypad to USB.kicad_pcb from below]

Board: 2 copper layers, 72.4 x 45.1 mm, 8 parts (2 on the bottom side), 19 nets.
